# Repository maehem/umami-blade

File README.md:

# umami-blade
Handheld JavaFX Gaming Platform

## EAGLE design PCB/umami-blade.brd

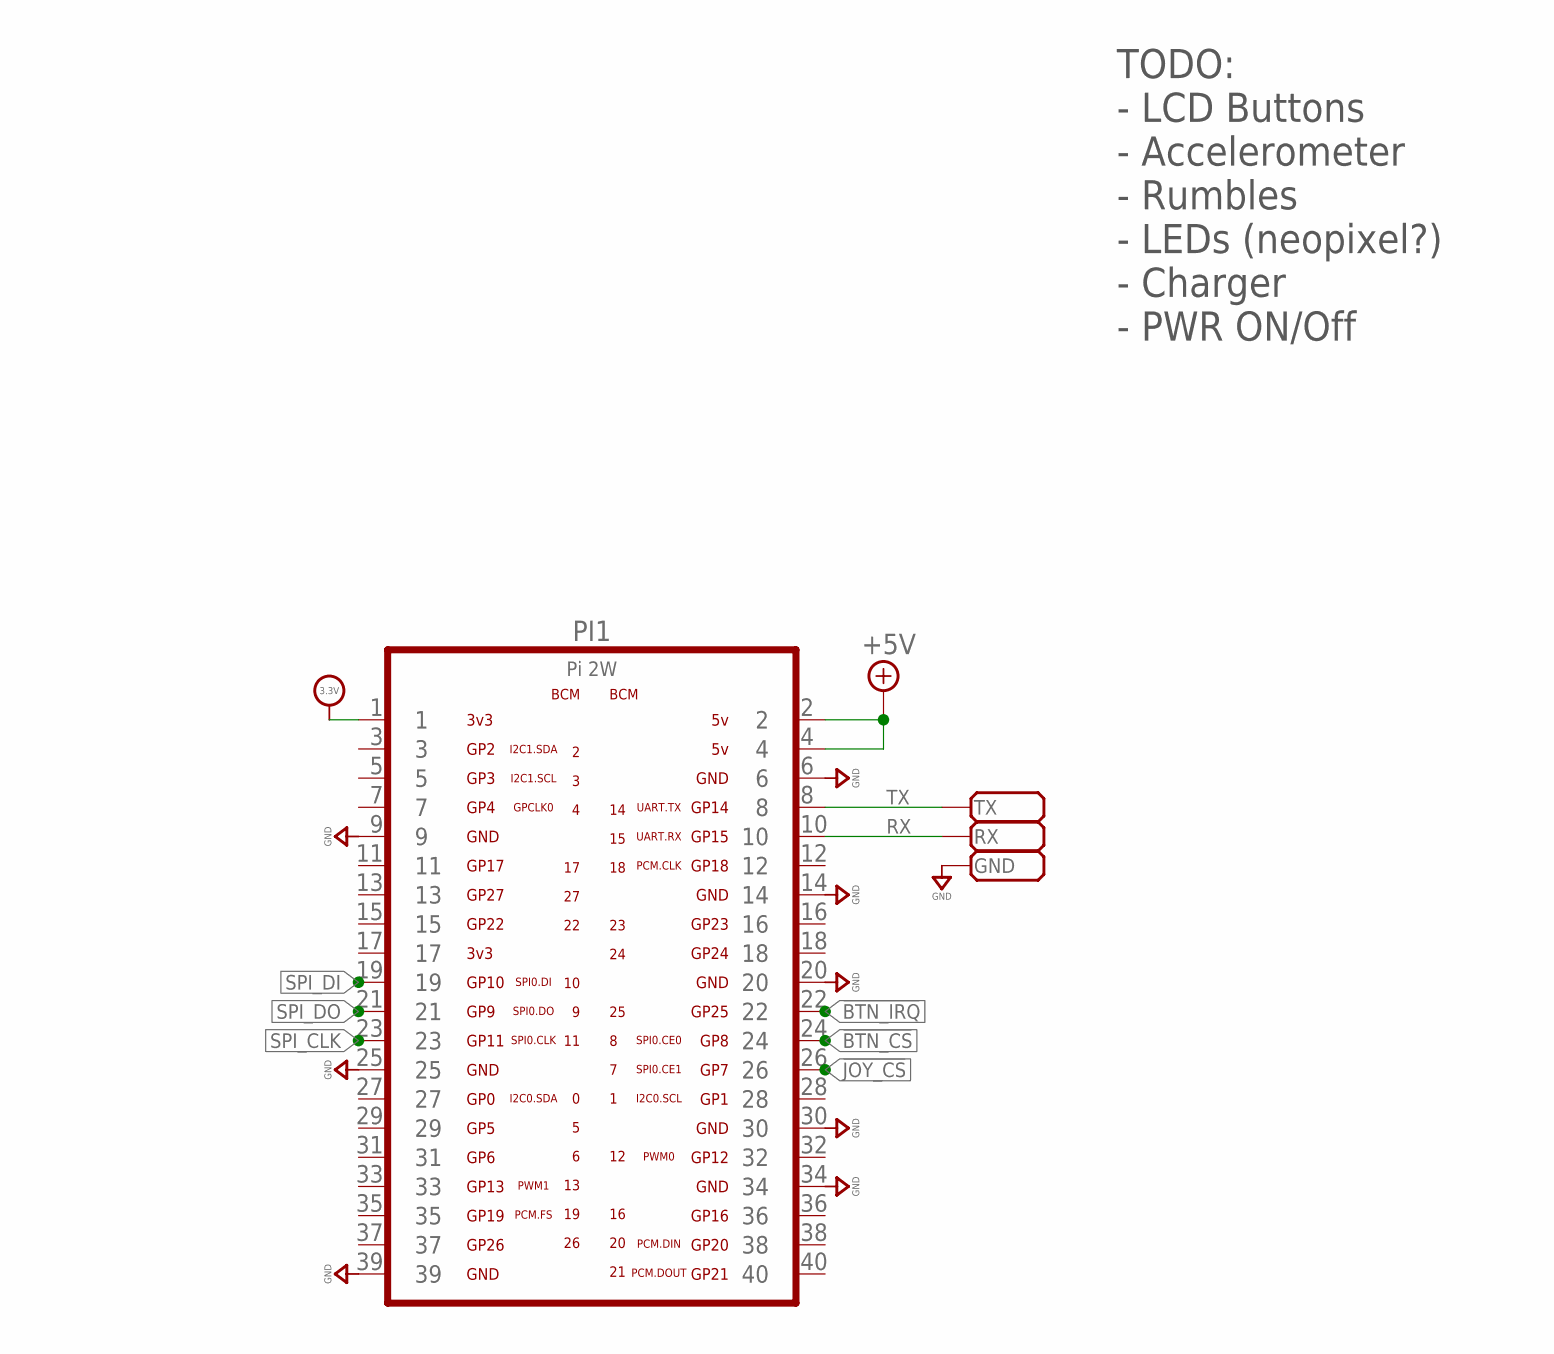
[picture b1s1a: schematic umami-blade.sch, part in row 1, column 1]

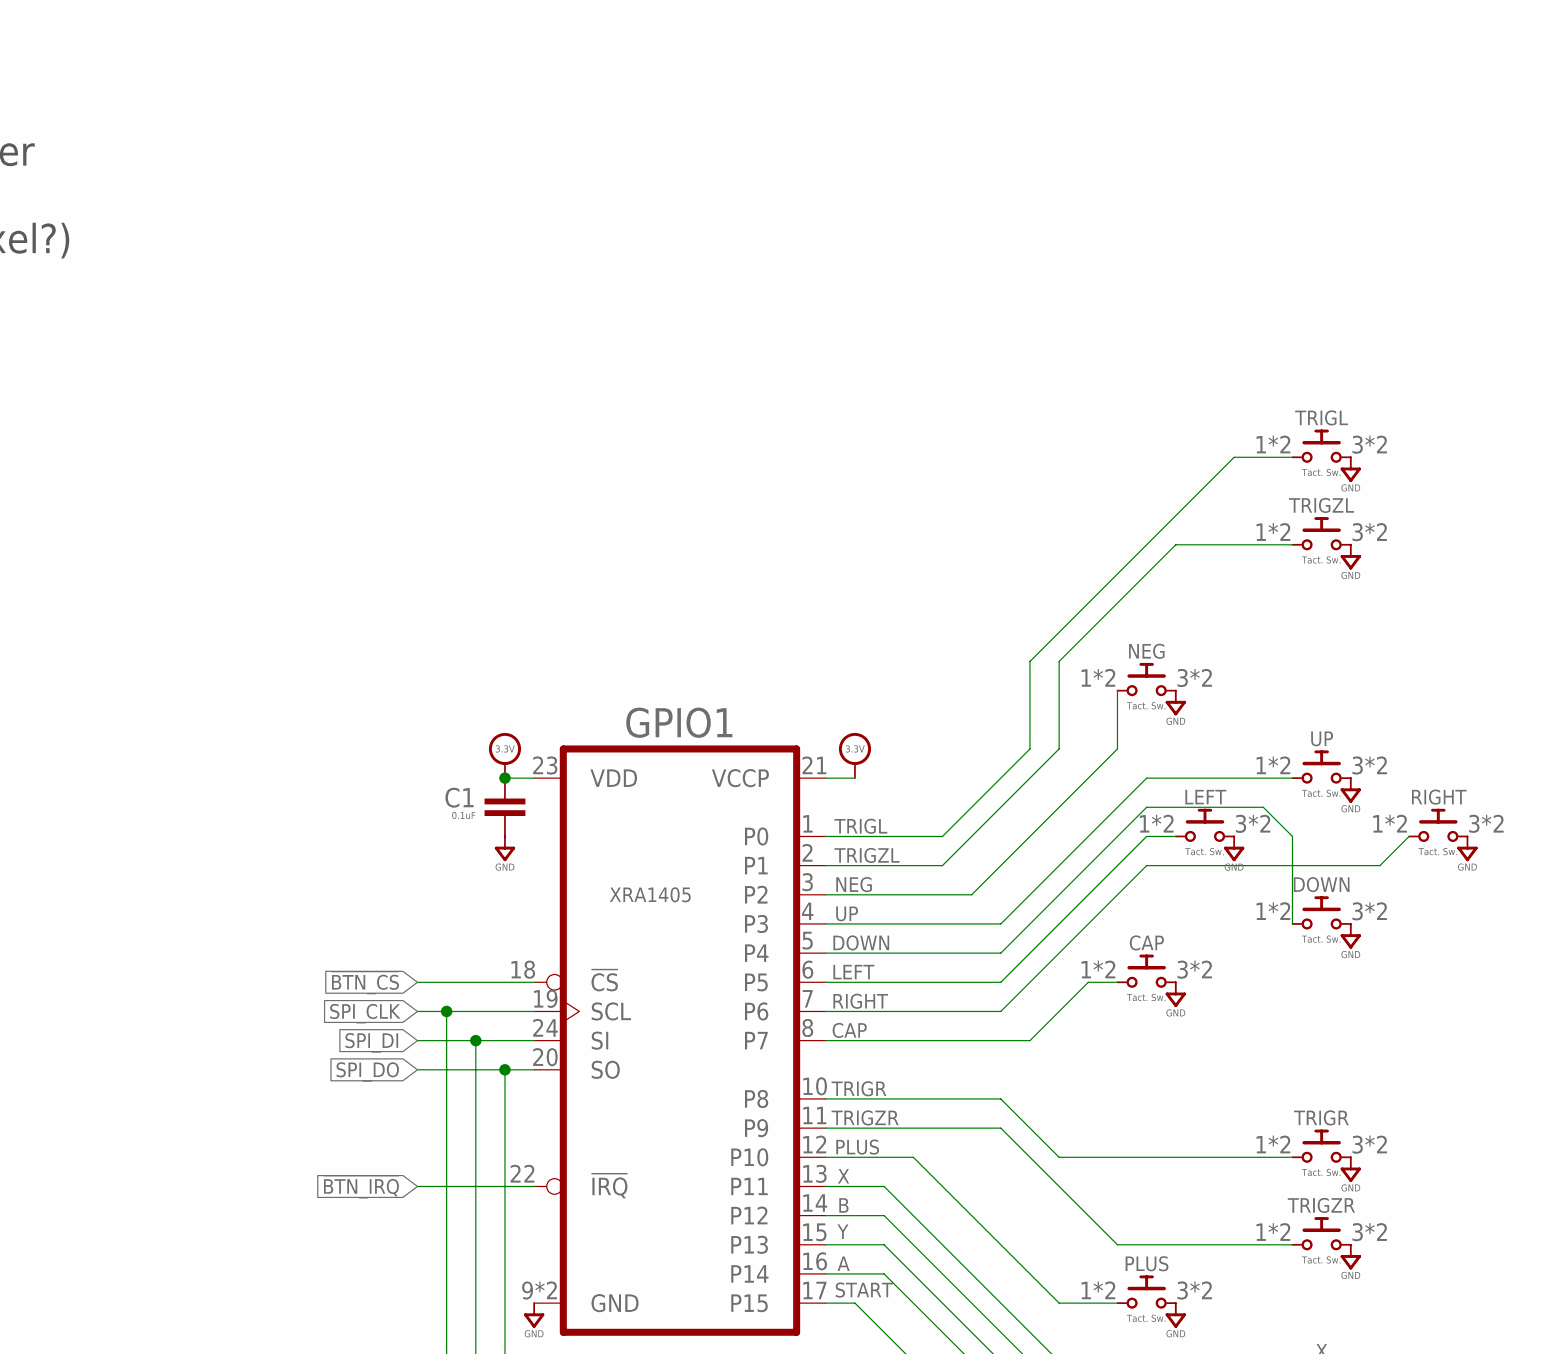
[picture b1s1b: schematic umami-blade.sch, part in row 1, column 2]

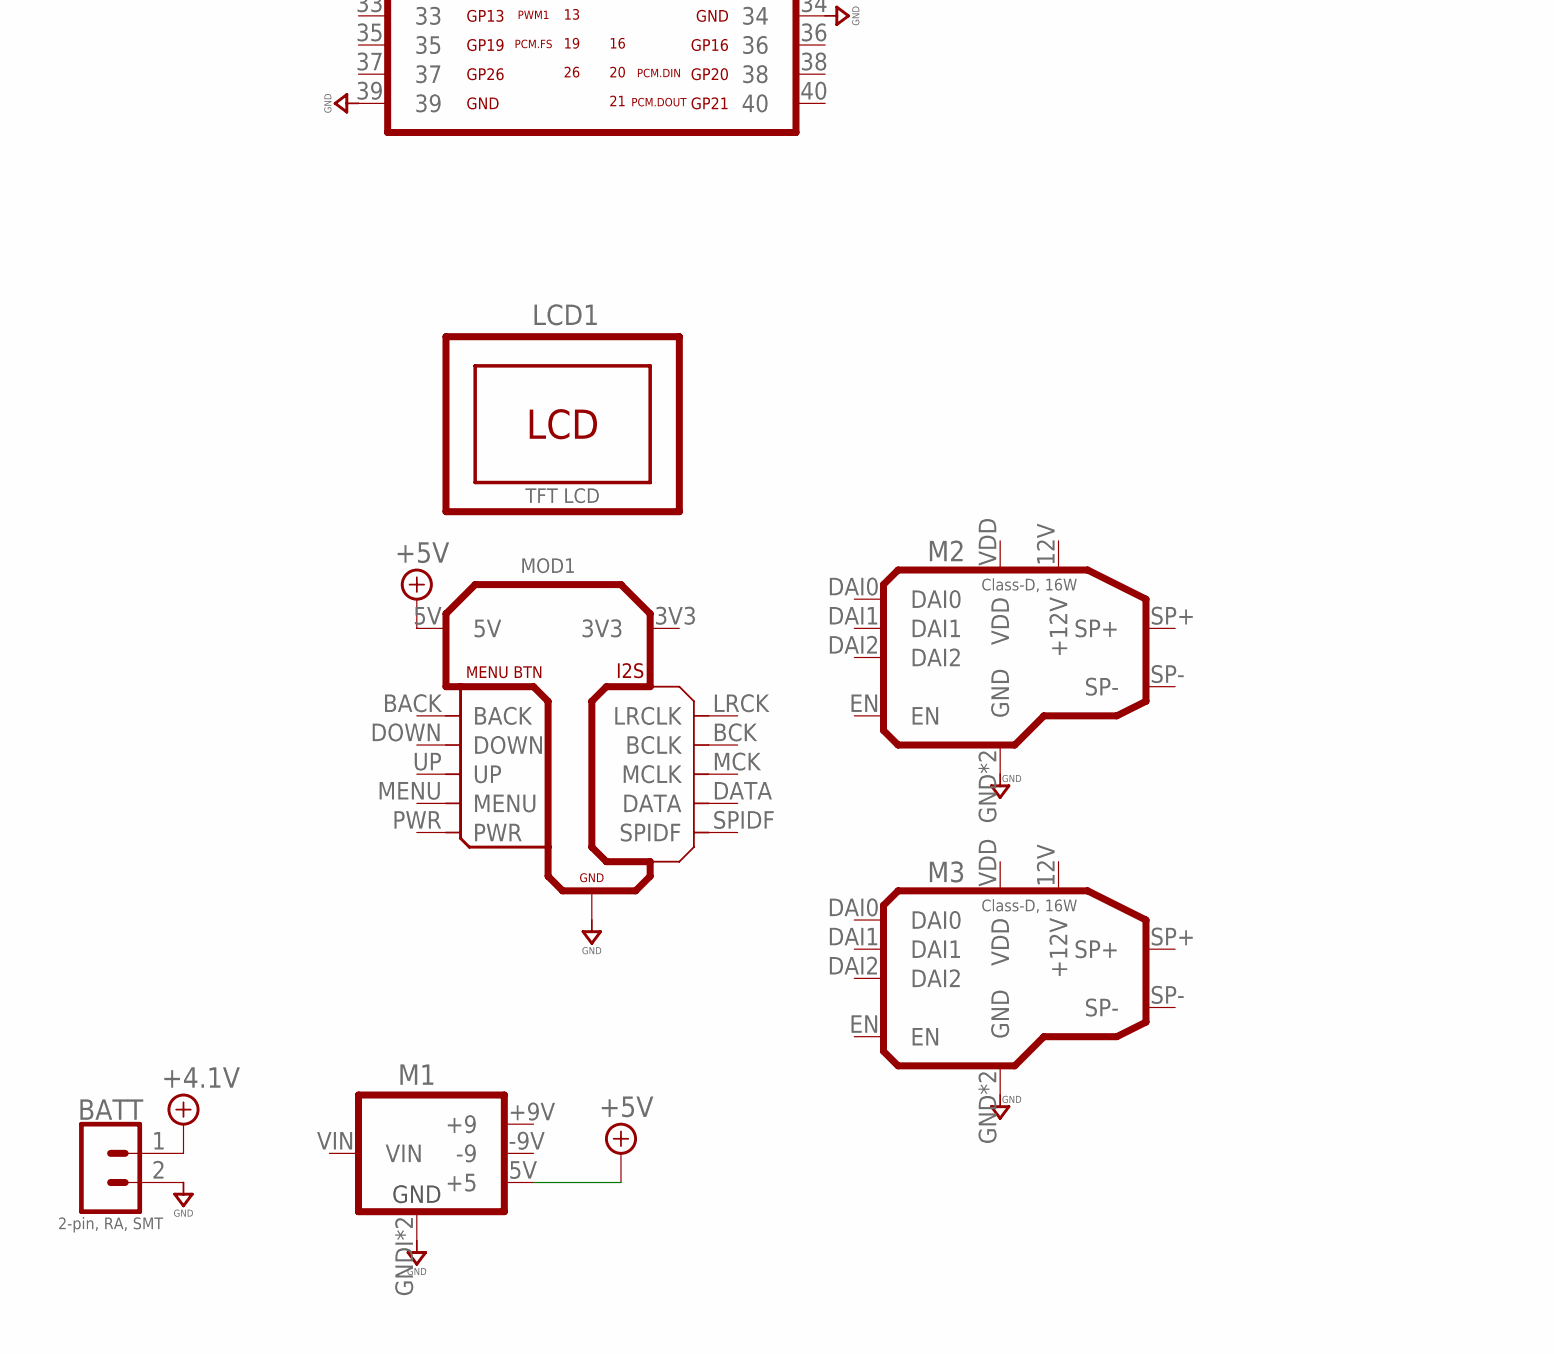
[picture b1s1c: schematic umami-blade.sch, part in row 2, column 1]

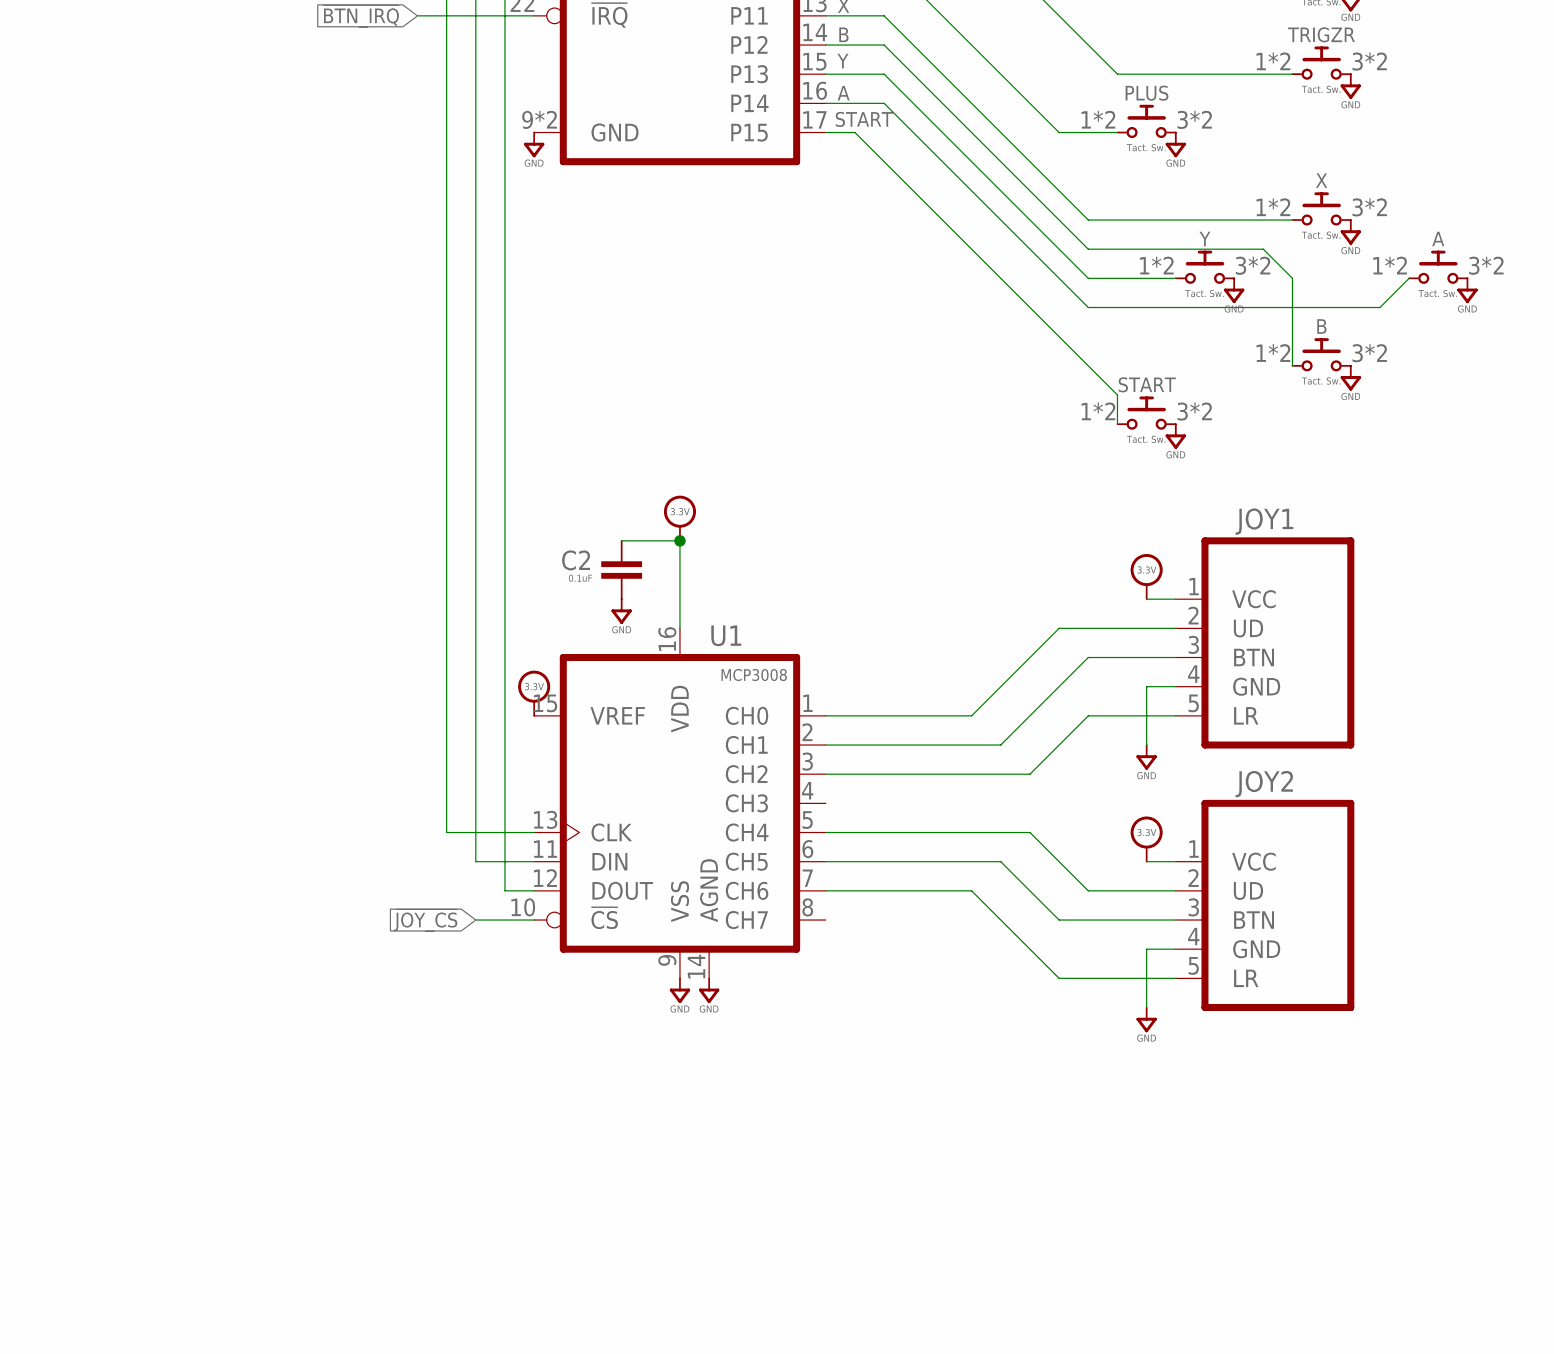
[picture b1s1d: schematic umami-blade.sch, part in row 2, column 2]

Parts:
A: Tact. Sw.; B3FS
B: Tact. Sw.; B3FS
BATT: 2-pin, RA, SMT; S2B-PH-SM4-
C1, C2: 0.1uF; 0603-CAP
CAP: Tact. Sw.; B3FS
DOWN: Tact. Sw.; B3FS
GND: PADSMD-050X050; SMD-050X050
GPIO1: XRA1405; QFN-24
JOY1, JOY2: THUMBSTICKNINTENDO-SWITCH; NINTENDO-JOYCON
LCD1: TFT LCD; PIMORONI_PIM372
LEFT: Tact. Sw.; B3FS
M1: 0128REV-A; 0128A
M2, M3: Class-D, 16W; 0123A
MOD1: LCD_CONTROLLERPIMORONI-8IN; PIMORONI-LCD-CONTROLLER
NEG: Tact. Sw.; B3FS
PI1: Pi 2W; PI-ZERO-2W
PLUS: Tact. Sw.; B3FS
RIGHT: Tact. Sw.; B3FS
RX: PADSMD-050X050; SMD-050X050
START: Tact. Sw.; B3FS
TRIGL: Tact. Sw.; B3FS
TRIGR: Tact. Sw.; B3FS
TRIGZL: Tact. Sw.; B3FS
TRIGZR: Tact. Sw.; B3FS
TX: PADSMD-050X050; SMD-050X050
U1: MCP3008; SO16
UP: Tact. Sw.; B3FS
X: Tact. Sw.; B3FS
Y: Tact. Sw.; B3FS

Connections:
!BTN_CS: GPIO1.18 (!CS), PI1.24
!BTN_IRQ: GPIO1.22 (!IRQ), PI1.22
!JOY_CS: PI1.26, U1.10 (!CS)
+3.3V: C1.1, C2.1, GPIO1.21 (VCCP), GPIO1.23 (VDD), JOY1.1 (VCC), JOY2.1 (VCC), PI1.1, U1.15 (VREF), U1.16 (VDD)
+4.1V: BATT.1
+5V: M1.5V (+5), MOD1.5V, PI1.2, PI1.4
A: A.1, A.2 (1), GPIO1.16 (P14)
B: B.1, B.2 (1), GPIO1.14 (P12)
CAP: CAP.1, CAP.2 (1), GPIO1.8 (P7)
DOWN: DOWN.1, DOWN.2 (1), GPIO1.5 (P4)
GND: A.3 (2), A.4 (2), B.3 (2), B.4 (2), BATT.2, C1.2, C2.2, CAP.3 (2), CAP.4 (2), DOWN.3 (2), DOWN.4 (2), GND.1, GPIO1.9 (GND), GPIO1.PAD (GND), JOY1.4 (GND), JOY2.4 (GND), LEFT.3 (2), LEFT.4 (2), M1.GNDI (GND), M1.GNDO (GND), M2.GND, M2.GND2 (GND), M3.GND, M3.GND2 (GND), MOD1.GND@I2S (GND), MOD1.GND@MENU (GND), NEG.3 (2), NEG.4 (2), PI1.6, PI1.9, PI1.14, PI1.20, PI1.25, PI1.30, PI1.34, PI1.39, PLUS.3 (2), PLUS.4 (2), RIGHT.3 (2), RIGHT.4 (2), START.3 (2), START.4 (2), TRIGL.3 (2), TRIGL.4 (2), TRIGR.3 (2), TRIGR.4 (2), TRIGZL.3 (2), TRIGZL.4 (2), TRIGZR.3 (2), TRIGZR.4 (2), U1.9 (VSS), U1.14 (AGND), UP.3 (2), UP.4 (2), X.3 (2), X.4 (2), Y.3 (2), Y.4 (2)
LEFT: GPIO1.6 (P5), LEFT.1, LEFT.2 (1)
unnamed: JOY1.3 (BTN), U1.2 (CH1)
unnamed: JOY1.2 (UD), U1.1 (CH0)
unnamed: JOY1.5 (LR), U1.3 (CH2)
unnamed: JOY2.2 (UD), U1.5 (CH4)
unnamed: JOY2.5 (LR), U1.7 (CH6)
unnamed: JOY2.3 (BTN), U1.6 (CH5)
NEG: GPIO1.3 (P2), NEG.1, NEG.2 (1)
PLUS: GPIO1.12 (P10), PLUS.1, PLUS.2 (1)
RIGHT: GPIO1.7 (P6), RIGHT.1, RIGHT.2 (1)
RX: PI1.10, RX.1
SPI_CLK: GPIO1.19 (SCL), PI1.23, U1.13 (CLK)
SPI_DI: GPIO1.24 (SI), PI1.19, U1.11 (DIN)
SPI_DO: GPIO1.20 (SO), PI1.21, U1.12 (DOUT)
START: GPIO1.17 (P15), START.1, START.2 (1)
TRIGL: GPIO1.1 (P0), TRIGL.1, TRIGL.2 (1)
TRIGR: GPIO1.10 (P8), TRIGR.1, TRIGR.2 (1)
TRIGZL: GPIO1.2 (P1), TRIGZL.1, TRIGZL.2 (1)
TRIGZR: GPIO1.11 (P9), TRIGZR.1, TRIGZR.2 (1)
TX: PI1.8, TX.1
UP: GPIO1.4 (P3), UP.1, UP.2 (1)
X: GPIO1.13 (P11), X.1, X.2 (1)
Y: GPIO1.15 (P13), Y.1, Y.2 (1)

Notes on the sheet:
TODO: - LCD Buttons - Accelerometer - Rumbles - LEDs (neopixel?) - Charger - PWR ON/Off

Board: 2 copper layers, 32 parts (3 on the bottom side), 33 nets, no tracks yet.

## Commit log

2022-05-17 PCB files added.
2022-09-30 progress
2022-10-02 Create KiCAD version of PCB
2026-01-14 Work in progress check-in.
